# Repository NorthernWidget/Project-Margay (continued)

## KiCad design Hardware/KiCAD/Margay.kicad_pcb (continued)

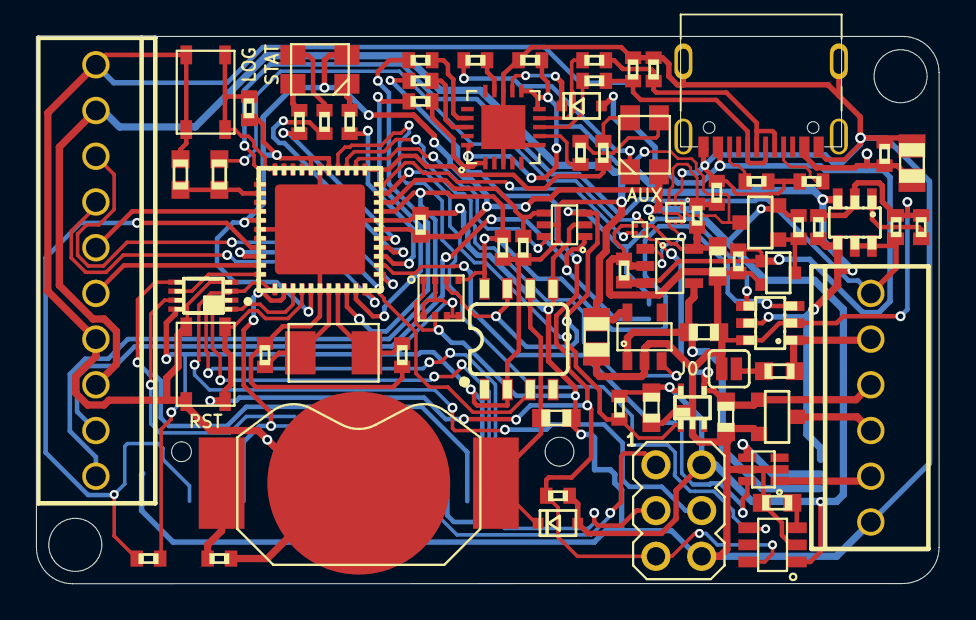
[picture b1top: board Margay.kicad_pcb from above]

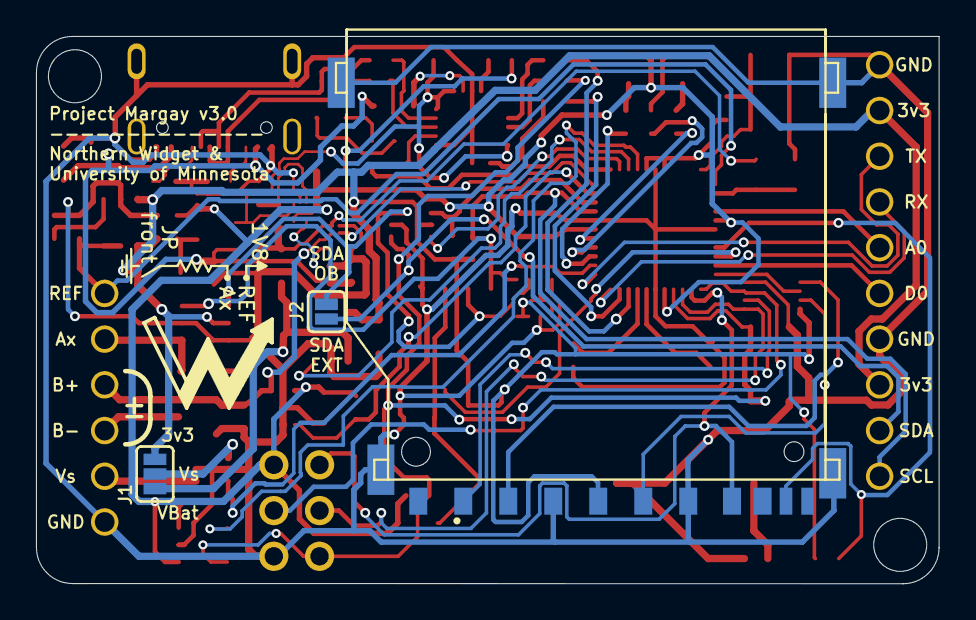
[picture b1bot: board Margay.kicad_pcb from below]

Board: 2 copper layers, 50.1 x 30.4 mm, 84 parts (4 on the bottom side), 72 nets.

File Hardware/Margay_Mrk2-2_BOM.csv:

"Qty","Value","Device","Package","Parts","Description","DIGIKEY","DISP","MF","MOUSER","MPN","PROD_ID","VALUE","VALUE_PART",
"1","","CONN_102.54_SCREW","1X10_SCREW","J2","Genaric 10 terminal header","ED10567-ND","","On Shore","","OSTVN10A150","","","",
"11","0.1uF","C-EU0.1UFC0402","C0402","C1, C4, C5, C9, C10, C11, C12, C16, C17, C18, C19","CAPACITOR, European symbol","490-4759-1-ND","","Murata","","GCM155R71C104KA55D","","","",
"2","100k","R-EU_100KR0402","R0402","R10, R19","RESISTOR, European symbol","311-100KLRCT-ND","","Yageo","","RC0402FR-07100KL","","","100k",
"9","10k","R-EU_10KR0402","R0402","R1, R2, R14, R15, R16, R17, R18, R20, R21","RESISTOR, European symbol","311-10.0KLRCT-ND","","Yageo","","RC0402FR-0710KL","","","10k",
"2","10k","R-EU_10KR0603","R0603","R22, R23","RESISTOR, European symbol","311-10.0KHRCT-ND","","Yageo","","RC0603FR-0710KL","","","10k",
"1","10k","R-EU_P10KR0603","R0603","R24","RESISTOR, European symbol","P10KDBCT-ND","","Panasonic","","ERA-3AEB103V","","","10k",
"2","10uF","C-EU10UFC0805","C0805","C6, C15","CAPACITOR, European symbol","490-6473-6-ND","","Murata","","GRM21BR61C106KE15K","","","",
"4","12pF","C-EU12PFC0402","C0402","C2, C3, C7, C8","CAPACITOR, European symbol","445-5585-1-ND","","TDK","","CGA2B2C0G1H120J050BA","","","",
"2","1k","R-EU_1KR0402","R0402","R7, R9","RESISTOR, European symbol","311-1.00KLRCT-ND","","Yageo","","RC0603FR-07330RL","","","1k",
"2","1uF","C-EU1UFC0603","C0603","C13, C14","CAPACITOR, European symbol","587-1251-1-ND","","Yaiyo Yuden","","EMK107BJ105KA-T","","","",
"2","27","R-EU_27R0402","R0402","R3, R4","RESISTOR, European symbol","YAG3086CT-ND","","Yageo","","RC0402FR-0727RL","","","27",
"1","2N7002","MOSFET-NCH-2N7002PW","SOT323","Q3","N-channel MOSFETs","2N7002W-FDICT-ND","","Diodes Incorporated","","2N7002W-7-F","TRANS-11151","2N7002","",
"6","330","R-EU_330R0402","R0402","R5, R6, R8, R11, R12, R13","RESISTOR, European symbol","311-330LRCT-ND","","Yageo","","RC0402FR-07330RL","","","330",
"1","ATMEGA1284M","ATMEGA1284M","MLF44-TH","U1","8-bit Microcontroller with 128K Bytes In-System Programmable Flash","ATMEGA1284P-MURCT-ND","","Atmel","","ATMEGA1284P-MUR","","","",
"1","AVRISP-6","AVRISP-6","AVRISP","ISP1","AVR ISP HEADER","609-3234-ND","","Amphenol","","67997-206HLF","","","",
"1","BAT43WS","DIODESOD-323","SOD323-R","D1","Genaric Diode","BAT43WS-FDICT-ND","","Diodes Incorporated","","BAT43WS-7-F","","","",
"1","BATTERY_COIN12MM","BATTERY_COIN12MM","LINX_BAT-HLD-012-SMT","BT1","Coin Cell Battery Holder","BAT-HLD-012-SMT-ND","","Linx","","BAT-HLD-012-SMT","","","",
"1","BME280","BME280","BME280","U12","BME280 - Combined Digital Humidity and Pressure Sensor","828-1063-1-ND","BME280","Bosch","","BME280","","","",
"2","BUTTON4.2X3.2","BUTTON4.2X3.2","SWITCH_4.2X3.2","S1, S2","Genaric SPST Pushbutton","CKN10504CT-ND","","C&K","","PTS810 SJG 250 SMTR LFS","","","",
"2","CLVBA-FKA","CLVBA-FKA","CLVBA-FKA","D2, D3","Cree RGB LED, Small Package, Common Anode, CLVBA-FKA","CLVBA-FKA-CAEDH8BBB7A363CT-ND","","Cree","","CLVBA-FKA-CAEDH8BBB7A363","","","",
"1","CONN_6SCREW_2.54","CONN_6SCREW_2.54","1X06_SCREW","J3","Genaric 6 terminal header","ED10565-ND","","OnShore","","OSTVN06A150","","","",
"1","CRYSTAL8MHZ5X3.2","CRYSTAL8MHZ5X3.2","CRYSTAL_5X3.2_2-SMD","XTAL1","Crystal Oscilator","887-1740-1-ND","","TXC","","7A-8.000MAAE-T","","","",
"1","DMG3404","MOSFET-NCH-DMG3404L","SOT23-3","Q1","N-channel MOSFETs","DMG3404L-7DICT-ND","","Diodes Incorporated","","DMG3404L-7","","DMG3404","",
"1","DS3231M","DS3231M","SO08","RTC1","DS3231M Real Time Clock","DS3231MZ+-ND","","Maxim","","DS3231MZ+","","","",
"1","FDN360P","MOSFET_PCH-FDN360P","SOT23-3","Q2","P-channel MOSFETs","FDN360PCT-ND","","Fairchild","","FDN360P","","FDN360P","",
"1","FT231X-Q","FT231X-Q","QFN20","U2","FT231x - USB to UART Bridge","768-1128-1-ND","","FTDI","","FT231XQ-R","","","",
"1","JUMPER-SMT_2_NC_PASTE_SILK","JUMPER-SMT_2_NC_PASTE_SILK","SMT-JUMPER_2_NC_PASTE_SILK","JP3","Normally closed solder jumper","","","","","","","","",
"1","JUMPER-SMT_2_NO_SILK","JUMPER-SMT_2_NO_SILK","SMT-JUMPER_2_NO_SILK","JP1","Normally open jumper","","","","","","","","",
"1","JUMPER-SMT_3_1-NC_PASTE_SILK","JUMPER-SMT_3_1-NC_PASTE_SILK","SMT-JUMPER_3_1-NC_PASTE_SILK","JP2","Normally closed solder jumper (1 of 2 connections)","","","","","","","","",
"1","MAX6070AAUT18","MAX6070AAUT18","SOT23-6L","U13","MAX6070 Low Noise high precision voltage referance","MAX6070BAUT18+TCT-ND","","Maxim","","MAX6070BAUT18+T","","","",
"1","MCP3421A1","MCP3421A1","SOT23-6L","U14","MCP342* - Sigma Delta ADC","MCP3421A1T-E/CHCT-ND","MCP3421","Microchip","","MCP3421A1T-E/CH","","","",
"1","MIC94090C6","MIC94090C6","SC-70_6","U11","MIC9409x - Hight Side Load Switch","576-3484-1-ND","MIC94090","Microchip","","MIC94090YC6-TR","","","",
"1","MICRO_USB_LONGPADS","MICRO_USB_LONGPADS","10118194-0001LF_10118194-0001LF_LONGER_PADS","USB1","","609-4618-1-ND","","Amphenol","","10118194-0001LF","","","",
"1","SDMMC06132","SDMMC06132","06132","J1","SD MMC Card holder","A101492CT-ND","","TE","","2041021-4","","","",
"1","SN74AUP3G34DCU","SN74AUP3G34DCU","DCU_(R-PDSO-G8)","U5","SN74AUP3G34 - Logic Buffer","296-25595-1-ND","","TI","","SN74AUP3G34DCUR","","","",
"1","SN74LVC1G3157DRL","SN74LVC1G3157DRL","DRL_R-PDSO-N6","U4","SN74LVC1G3157 - SPDT Analog Switch","296-18015-1-ND","SN74LVC1G3157","TI","","SN74LVC1G3157DRLR","","","",
"1","TLV3691DPF","TLV3691DPF","DPF0006A","U10","TLV3691 - Nanopower Analog Comparator","296-37242-6-ND","","TI","","TLV3691IDPFR","","","",
"1","TPL5010DDC","TPL5010DDC","DDC_R-PDSO-G6","U3","TPL5010 - Nano-Power System Timer with Watchdog Functionality","296-38829-1-ND","","TI","","TPL5010DDCT","","","",
"1","TPS2104","TPS2104","SOT23-5","U9","TPS210x - Power Distribution Switch (OR'ing switch)","296-10882-1-ND","TPS2104","TI","","TPS2104DBVR","","","",
"1","TPS22916YFP","TPS22916YFP","YFP0004","U8","TPS22916 - Ultra Low Leakage Load Switch","296-47464-1-ND","","TI","","TPS22916CYFPT","","","",
"1","TPS79733","TPS79733","DCK_R-PDSO-G5","U6","TPS797* - Ultra Low Power Low Dropout Linear Regulator","296-11990-1-ND","TPS79733","TI","","TPS79733DCKR","","","",
"1","TPS7A0533DBV","TPS7A0533DBV","SOT23-5","U7","TPS7A05* - Ultra Low Power Low Dropout Linear Regulator","296-50256-1-ND","","TI","595-TPS7A0533PDBVR","TPS7A0533PDBVR","","","",

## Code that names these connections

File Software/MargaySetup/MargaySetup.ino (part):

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const uint8_t ThermSense_Pin = 1;
const uint8_t BatSense_Pin = 2;

const uint8_t VSwitch_Pin = 12;
const uint8_t SD_CD = 1;

const uint8_t Ext3v3Ctrl = 19;
const uint8_t ExtInt = 11;
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
const uint8_t RGB[] = {RED, GREEN, BLUE};

const int SD_CS = 4;
char FileNameC[11];
boolean SD_Init = false;

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}

void IOTest() {
  pinMode(VSwitch_Pin, OUTPUT);
  pinMode(ExtInt, OUTPUT);

  while(Serial.read() != '\r') {
    digitalWrite(VSwitch_Pin, LOW);
    digitalWrite(ExtInt, LOW);
    delay(1000);
    digitalWrite(VSwitch_Pin, HIGH);
    digitalWrite(ExtInt, HIGH);
    delay(1000);
  }
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
boolean TestSD() {
  boolean SDError = false;
  pinMode(SD_CS, OUTPUT);
  SPI.setDataMode(SPI_MODE0);
  SPI.setClockDivider(SPI_CLOCK_DIV2);

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
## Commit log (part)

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2018-03-01 First commit, schematic complete, board routing in progress
2018-03-01 Preliminary layout done, fixed led issue
    Finished with first round layout, changed supply voltage for LEDs to be 3v3 instead of VUSB so that alive led can work regardless of use of USB voltage
2018-03-02 Edits for 0.1"compatability
2018-03-03 Minor edits, generated gerbers
2018-03-06 Final Gerbers, renamed design
2018-04-04 updated readme again
    Added software description to readme, software to be promptly added!
2018-04-04 Added software folder to repo
    Software folder containing hardware test script as well as logger code which supports the TP-Downhole
2018-04-04 Updated readme
    Updated DS3231_Logger link in readme, now that this repo actually exists
2018-04-09 Minor moddifications to software
2018-04-09 Added revision notes to board
2018-04-11 Margay 1.0 initial layout
    Initial layout of the version 1.0 , solder jumpers currently not added, along with battery connector, may intoduce back later, needs cleanup and DRC
2018-04-12 Cleaned up board, removed power switch
    Cleaned up the routing, removed the switched power
2018-04-12 Updated board, fixed software logging time
    Cleaned up traces on board, changed battery in schematic, updated logging program to have 15 minute interval by default
2018-04-16 Generated gerbers, ready for Mrk1
2018-04-16 Fixed silk screen in gerbers
2018-05-03 Added stencil files and updated/fixed logger code
    Added solder stencil files and fixed the temp conversion issue in the logger code, and added a blink to indicate when the log button is pressed
2018-05-03 Edits to software for default time and baro mode
    Added dedicated baro sketch file, and changed default saved logging time to be 15 minutes s
2018-06-01 Minor mod to hardware test, added BOM
    Added independent BOM and did some clean up on the schematic
2018-06-01 Added frames, major schematic clean up
    Added frames and cleaned up and divided schematic into additional sheets
2018-06-06 Updated board to account for part changes
    Fixed issue where 2x1 connectors displaced, also updated passives to new sizes
2018-06-06 Updated passive size
2018-06-06 Changed folder arraignment
2018-06-13 semicolons to commas in CSV
2018-06-28 Updated test files, pick and place info, and fixed part info
2018-06-28 Updated licence
2018-07-12 Added reference designators and legacy hardware test
    Added legacy hardware testing file and reference designator image
2018-09-07 Software power fix in hardware test, added dedicated v0 and v1 test scripts
    Changed power sequencing in the hardware test script, added a dedicated v0 and v1 version for the Margay test file
2018-09-07 Fixed button layout (#14)
    Updated button layout from Cold Silicon updates, fixed resulting layout issues
2018-09-10 Cleaned up schematic, added board and schematic images for v1.0
    Added documentation for version 1.0, added schematic PDF, board images, and updated BOM to fix ADC part number
2018-09-10 First round of v2 updates to schematic
2018-09-14 Revised schematic for Margay v2, added circuit simulations
    Will remove some simulations later, still need to do much layout and placement, as well as verify the schematic
2018-09-14 Updated simulation names, gitignore, clean
    Cleaned out bulk files, changed simulation names, added LTSpice files to gitignore
2018-09-15 Begining of v2 layout
    Power section and severl problematic signals taken care of, still need to add BME280 and fix header connections
2018-09-17 Main v2 layout complete, needs review minor cleanup
    Main layout is completed, needs verification and review for any traces which need to be cleaned up. Double check power on schematic!
2018-09-18 Cleanup and silkscreen
    Cleanup of traces, minor fix to overlap problem, relabeled silk screen to match new connections
2018-09-26 1Mb file size
2018-09-26 Added pin description section to README
    Added list of pins and a brief description of their features to the readme
2018-10-02 Added developer notes to readme
2018-10-02 Fixed symbols in readme
    Forgot `&` in HTML symbol formatting in readme to OMEGA did not format properly
2018-10-31 Updated model info in readme
2018-10-31 Added note about 3.3v logic in readme
2019-01-05 Condensed headers, added bat cap, added WDT
    Condensed headers into 2 single piece headers, added capacitor on backup battery to deal with debouncing issue, also added WDT unit and replaced switched voltage output driver with unit switch instea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
2019-01-07 xtal cap GND tweak, E hdr flush
2019-01-07 label RTC_BAT+
2019-01-07 Updated to new battery
    Updated battery part to fix airwire issue
2019-03-20 In progress of power switch upgrade
    Midway through upgrade of power switch topology
2019-03-20 improvements to aux power switch, layout complete
    Completed layout of new aux power switch topology
2019-03-21 Updated paste patterns, generated paste gerbers
    Generated solder paste gerbers and updated paste layout to be more correct (~60% on body pads)
2019-03-21 Added v2 Gerbers
2019-04-03 Updates for v2.1
    Added in schematic and board updates for v2.1, voltage divider on input to comparator, and diode in series with FTDI
2019-04-13 v2.1, sent to fab
    Minor board cleanup and generated gerbers for fab
2019-04-21 CC BY-SA 4.0 International: official wording
2019-04-30 Added part numbers, moved part identifiers
2019-05-07 Changed auto power switch topology, cleanup desired
    Changed auto power switch to use active low logic
2019-05-12 Minor cleanup, generated gerbers, sent v2.2 to fab
2019-07-19 Minor edits and cleanup for manufacture submission
2019-07-31 2-page guide
2019-08-06 Added reference ID docs
2019-08-15 Cleaned up schematic and updated BoM for v2.2
2019-09-12 Updated BoM, corelated with schematic
    Fixed SD card issue, fixed 0603 vs 0402 issue
2020-04-26 rm outdated diagrams
2020-04-26 Pick and Place files a good idea, but these are outdated
2020-04-26 Outdated stencil files
2020-04-26 Duplicate of Margay.csv
2020-04-26 Presuming this renumbering is done, this file can live on in archives
2020-04-26 Fabrication layout diagrams to their own folder
2020-04-26 Earlier version
2020-04-26 v1 Gerbers
2020-04-26 rm 2.x Gerbers older than current revision
2020-04-26 Only one Gerber zip; no need for folder unless we break these out again
2020-04-26 rm v0 and v1 tests, etc.
2020-04-30 Battery and Margay box mounts; fab stencil
2020-05-01 GNU GPL v3 for code products (software, firmware, etc.)
2020-05-03 Labeled all jumpers, including Vdiv schematic
2020-06-06 Schematic images
2020-06-06 Vector diagram for analog jumper on silk
2020-06-06 Vdiv jumper on board front
2020-06-18 Sources of support
2020-06-18 Remove blank line between images
2021-02-20 Example code and notes on updated guide.
2021-02-28 scrapped initial changes (not good enough), left comments for intent
2021-02-28 ODT and PDF to git LFS
2021-02-28 Opaque white background to see black text
2021-03-01 Default Vs=Vswitch connected to 3V3_AUX via solder paste on jumper
2021-03-01 Swap + fix SDA OB and SDA EXT jumper labels
2021-03-02 Removed erroneous top silk
2021-03-02 Vdiv diagram on back for jp on front
2021-03-02 Zenodo DOI badge
2021-03-02 Added v2.2 Gerbers
2021-03-07 First round of document organizing
2021-03-10 On-board I2C, SPI, and UART devices
2021-03-11 Minor rewording
2021-03-12 Reformatting operation guide pt. 1
2021-03-12 Typo fix/note for myself for the future
2021-03-15 Small consistency changes: reorganizing lists, bolding, etc.
2021-04-02 shuffling tech specs, small changes
2021-04-06 reorganized sections, couple of typos
2021-04-07 Use carriage return or newline/linefeed
2021-04-07 Setting the serial number
2021-04-13 Initial final version
2021-04-13 Mounting plate for WQ-48 box Untested as of yet; if no new commits in a few days, it works!
2021-04-14 Holes for #4 screws; reposition resistors and traces
2021-04-16 No 4 screw holes: tight fit (ColdSilicon lbr)
2021-04-16 Updated for both orientations and No.4 holes
2021-04-16 Route SW trace to open space for metal stand-off
2021-05-10 100K 0402 --> 0603 for easier replacement This is on the WDT-setting resistor (R10) I changed a second resistor (R19) associated with the power system to fully convert the 0402s to 0603s and keep the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
2021-07-05 update "Margay_NoSensors.ino"
    Remove unused variables
    Make "header" lowercase per code style standards
2021-07-05 Margay_NoSensors: Update/fix comments
2021-07-17 Update sample code for library updates
    Margay can be instantiated without passing arguments
    Run --> run
2021-07-17 v2.3 on back silk
2021-07-19 ISP driver note
2021-07-19 margay blue logging blink updated
2021-08-08 note consistency changes
2021-08-08 note consistency changes pt. 2
2022-04-26 Update wire names: match code and silk
2022-05-01 USB-C conversion in progress: moving parts
2022-05-01 USB C: Components placed; routing
2022-05-01 USB-C: Routing complete; DRC passed
2022-05-02 ~65:47 WDT 130K resistor 0603 1 hour logging intervals seem like a common desire. Our 100K resistor reset the logger after ~59:40, permitting a dangerous edge case (that Yuan Zeng found) by which the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
2022-05-09 Fixes to v2.3 update
    - VUSB and VBUS connected
    - Moved vias from underneath USB connector
    - Separated Analog GND region from USB GND region to reduce noise
    - Fixed 3v3 routing (current limiting path between input and MCU)
    - Moved the "Project Margay" label on bottom to try to have it less disrupted by the solder-mask stops
2022-05-09 Updated 5.1kΩ resistors
    Updated 5.1kΩ resistors to use bschulz_passives library item
2022-05-18 Max voltage
    Absolute max in comment; recommended shows up in rendered Markdown
2022-06-22 LONG short short good flash
2022-10-12 Bobby Schulz' ORCID
2022-10-13 Update UMN ESCI image
2023-01-22 Incorrect license CC-BY-SA 4.0 is (see LICENSE.md)
2023-03-17 Updated parts for production
    - XTAL
    - XTAL Caps
    - Jumpers (DNP)
    - TPS2104
    - MAX6070
2023-03-17 Updated SD card and analog switch
2023-03-17 Updated BoMs
2023-03-20 2v2 BoM alongside others
2023-04-13 Updated readme for v2.2 and VSwitch info
    Added pinout info for v2.2 logger and added current/power output limits for VSwitch
2023-07-27 Added mount file for v3.0
2023-10-25 Revise license text to proper Markdown version.
2024-11-02 Added documentation and production info
2025-12-11 Change MAX 6071 to 6070 on v3.0 BoM by hand
    Unintentional v2.3 to 3.0 change: the 6070 is what we need. We should check if the 6071 or the 6070 is included in the PCB definition, now or once we transition to KiCAD.
    We noted this error because of faulty (doubled) battery-voltage readings in the cold.
    From Bobby Schulz, who found the source of the error:
    This is important because the MAX6071 does not have an internal filter and as a result the pinout changes - see Page 19 of datasheet. This pinout changes pin 1 from the filtered input (how we intende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
2026-06-01 3V3 --> Schottky diode --> VCoin+. Provide a backup option for the clock if its battery fails: the main batteries of the data logger. Ideally, this would have been connected to VBat to keep the coin 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
2026-06-01 Autoformat from one line.
2026-06-01 Add extra 1 uA decoupling cap for DS3231M. The 0.1uF cap is right by the battery, which is fine. But there was not as much buffering of power changes right by the DS3231M. And the DS3231M responds be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
    Claude Code did a quick calculation based on my finding of an up to 300 us
    lag: this is the time required for a VBat handoff.
    C = I × t / ΔV = 0.3 mA × 300 µs / 0.25 V = 0.36 µF
    This extra capacitor might not be necessary, but considering the importance
    of the RTC and the fact that we have space, I am aiming these commits to
    ensure that the RTC is properly buffered from power changes and stays running.
2026-06-01 Unify 10K resistors to CRT0603-BY-1002ELFCT-ND.
2026-06-01 Oval slots for USB C mechanical feet.
2026-06-02 Update pad-size defaults based on oval holes for USB C feet.
